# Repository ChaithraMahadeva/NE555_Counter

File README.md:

# NE555_Counter
Design and Implementation of NE555 Counter using KiCAD PCB Design Tool.

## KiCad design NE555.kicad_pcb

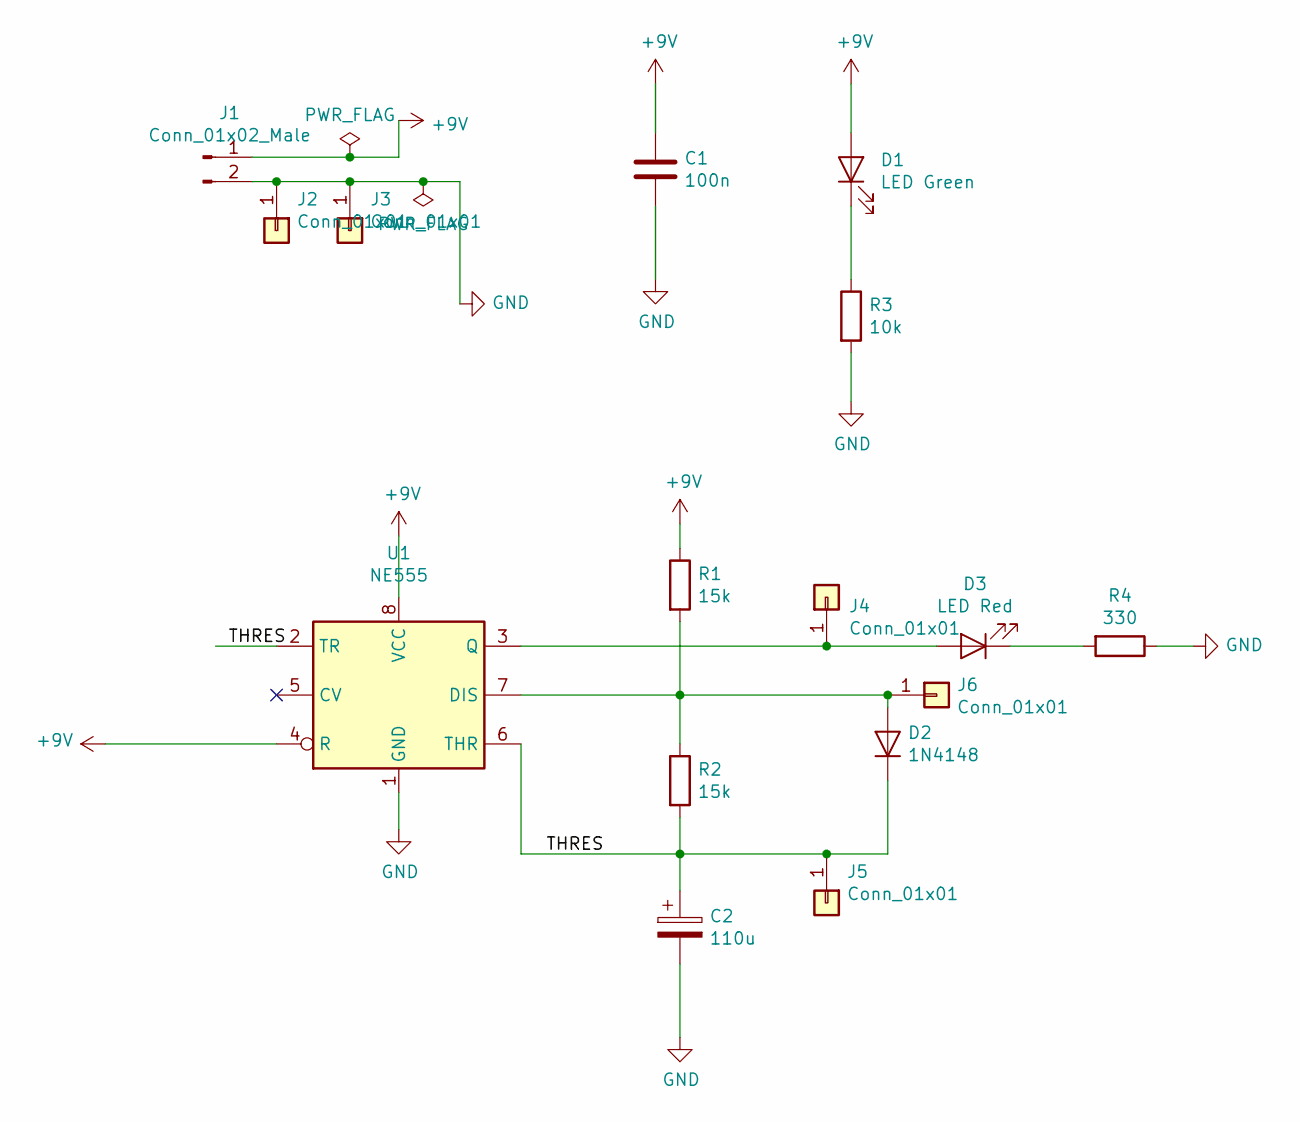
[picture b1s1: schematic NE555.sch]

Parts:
C1: 100n; C_Rect_L7.2mm_W2.5mm_P5.00mm_FKS2_FKP2_MKS2_MKP2
C2: 110u; CP_Radial_D6.3mm_P2.50mm
D1: LED Green; LED_1206_3216Metric_Pad1.42x1.75mm_HandSolder
D2: 1N4148; D_DO-35_SOD27_P7.62mm_Horizontal
D3: LED Red; LED_D5.0mm-3
J1: Conn_01x02_Male; PinHeader_1x02_P2.54mm_Vertical
J2, J3, J4, J5, J6: Conn_01x01; PinHeader_1x01_P2.54mm_Vertical
R1, R2: 15k; R_Axial_DIN0204_L3.6mm_D1.6mm_P7.62mm_Horizontal
R3: 10k; R_1206_3216Metric_Pad1.42x1.75mm_HandSolder
R4: 330; R_Axial_DIN0204_L3.6mm_D1.6mm_P7.62mm_Horizontal
U1: NE555; DIP-8_W7.62mm_Socket

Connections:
+9V: C1.1, D1.2 (A), J1.1, R1.1, U1.4 (R), U1.8 (VCC)
/THRES: C2.1, D2.1 (K), J5.1, R2.2, U1.2 (TR), U1.6 (THR)
GND: C1.2, C2.2, J1.2, J2.1, J3.1, R3.2, R4.1, U1.1 (GND)
unnamed: D1.1 (K), R3.1
unnamed: D2.2 (A), J6.1, R1.2, R2.1, U1.7 (DIS)
unnamed: D3.1 (K), R4.2
unnamed: D3.2 (A), J4.1, U1.3 (Q)

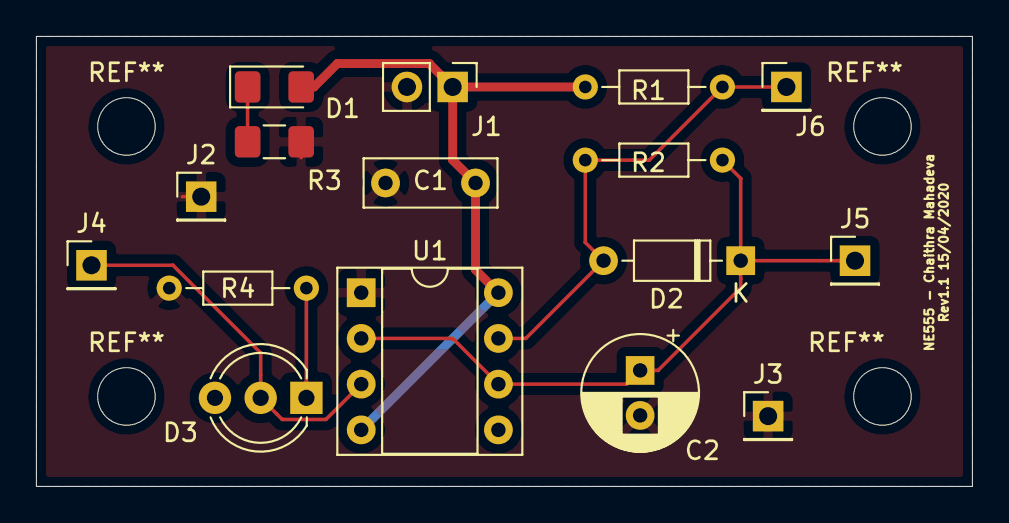
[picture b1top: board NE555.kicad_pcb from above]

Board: 2 copper layers, 52.0 x 25.0 mm, 16 parts (0 on the bottom side), 7 nets.
